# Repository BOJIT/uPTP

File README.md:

# uPTP

The smallest, cheapest PTP clock that you can make!

## Project Setup

1. Clone Project to your computer

2. Ensure that you have west installed somehere (I usually put it in `<GIT_REPO>/.venv`, as VSCode will usually launch it automatically.)

- `python -m venv .venv`
- `source .venv/bin/activate`
- `pip install west`

3. Run West Init Locally against the West YAML file: `west init -l software/app

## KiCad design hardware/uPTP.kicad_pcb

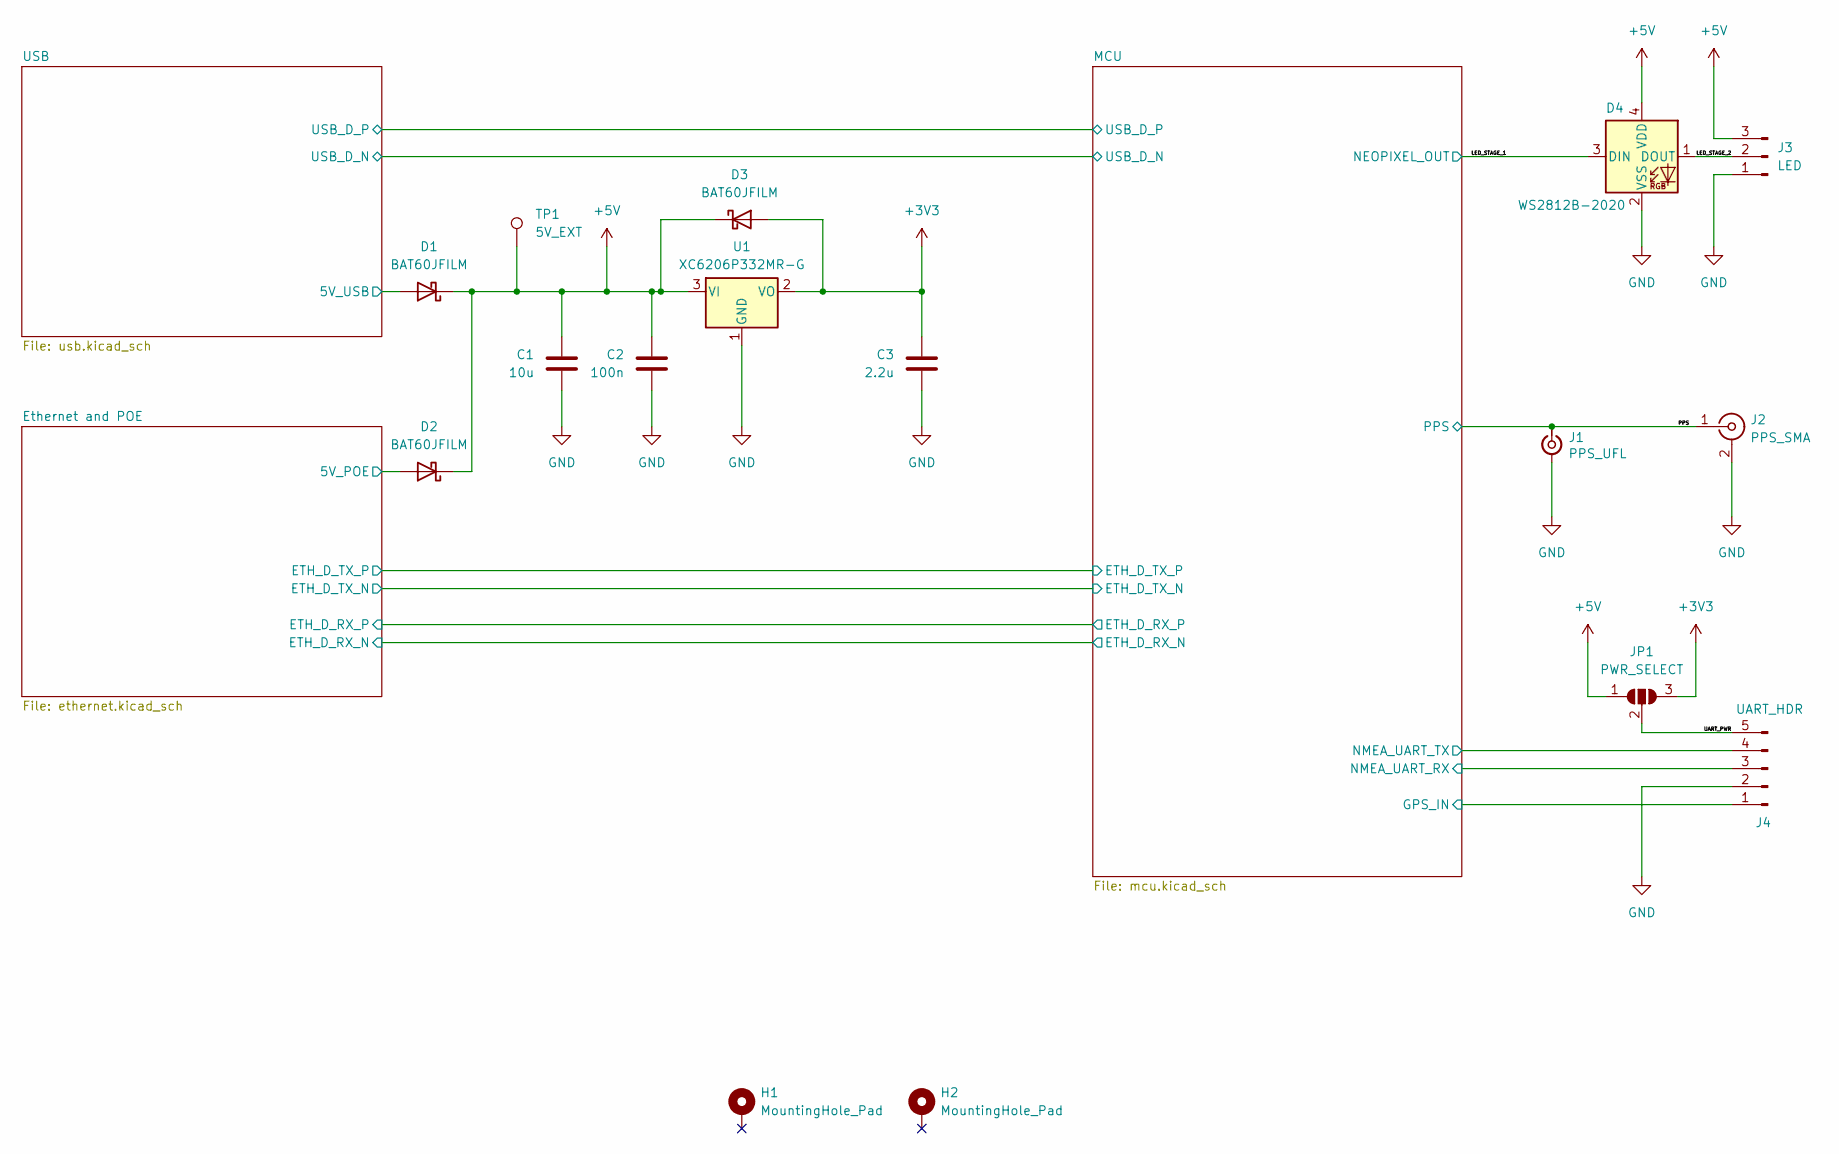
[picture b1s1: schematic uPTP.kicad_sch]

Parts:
C1: 10u; C_0603_1608Metric; LCSC Part C19702
C2: 100n; C_0402_1005Metric; LCSC Part C1525
C3: 2.2u; C_0402_1005Metric; LCSC Part C12530
D1, D2, D3: BAT60JFILM; D_SOD-323; LCSC Part C133103
D4: WS2812B-2020; LED_WS2812B-2020_PLCC4_2.0x2.0mm; LCSC Part C965555
H1, H2: MountingHole_Pad; MountingHole_3.2mm_M3_Pad
J1: PPS_UFL; IPEX-SMD_HC-RF-IPEX0303-01; LCSC Part C2894919
J2: PPS_SMA; SMA_Samtec_SMA-J-P-H-ST-EM1_EdgeMount
J3: LED; PinHeader_1x03_P1.27mm_Vertical
J4: UART_HDR; PinHeader_1x05_P2.54mm_Horizontal
JP1: PWR_SELECT; SolderJumper-3_P1.3mm_Open_RoundedPad1.0x1.5mm_NumberLabels
TP1: 5V_EXT; TestPoint_Pad_D1.5mm
U1: XC6206P332MR-G; SOT-23-3; LCSC Part C5446

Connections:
+3V3: C3.1, D3.2 (A), JP1.3 (B), U1.2 (VO); also elsewhere on the board
+5V: C1.1, C2.1, D1.1 (K), D2.1 (K), D3.1 (K), D4.4 (VDD), J3.3, JP1.1 (A), TP1.1, U1.3 (VI); also elsewhere on the board
+5V_USB: D1.2 (A); also elsewhere on the board
/Ethernet and POE/ETH_POE_FILT_P: D2.2 (A); also elsewhere on the board
/LED_STAGE_1: D4.3 (DIN); also elsewhere on the board
/LED_STAGE_2: D4.1 (DOUT), J3.2
/MCU/GPS_IN: J4.1; also elsewhere on the board
/MCU/NMEA_UART_RX: J4.3; also elsewhere on the board
/MCU/NMEA_UART_TX: J4.4; also elsewhere on the board
/PPS: J1.1 (In), J2.1 (In); also elsewhere on the board
/UART_PWR: J4.5, JP1.2 (C)
GND: C1.2, C2.2, C3.2, D4.2 (VSS), J1.2 (Ext), J2.2 (Ext), J3.1, J4.2, U1.1 (GND); also elsewhere on the board

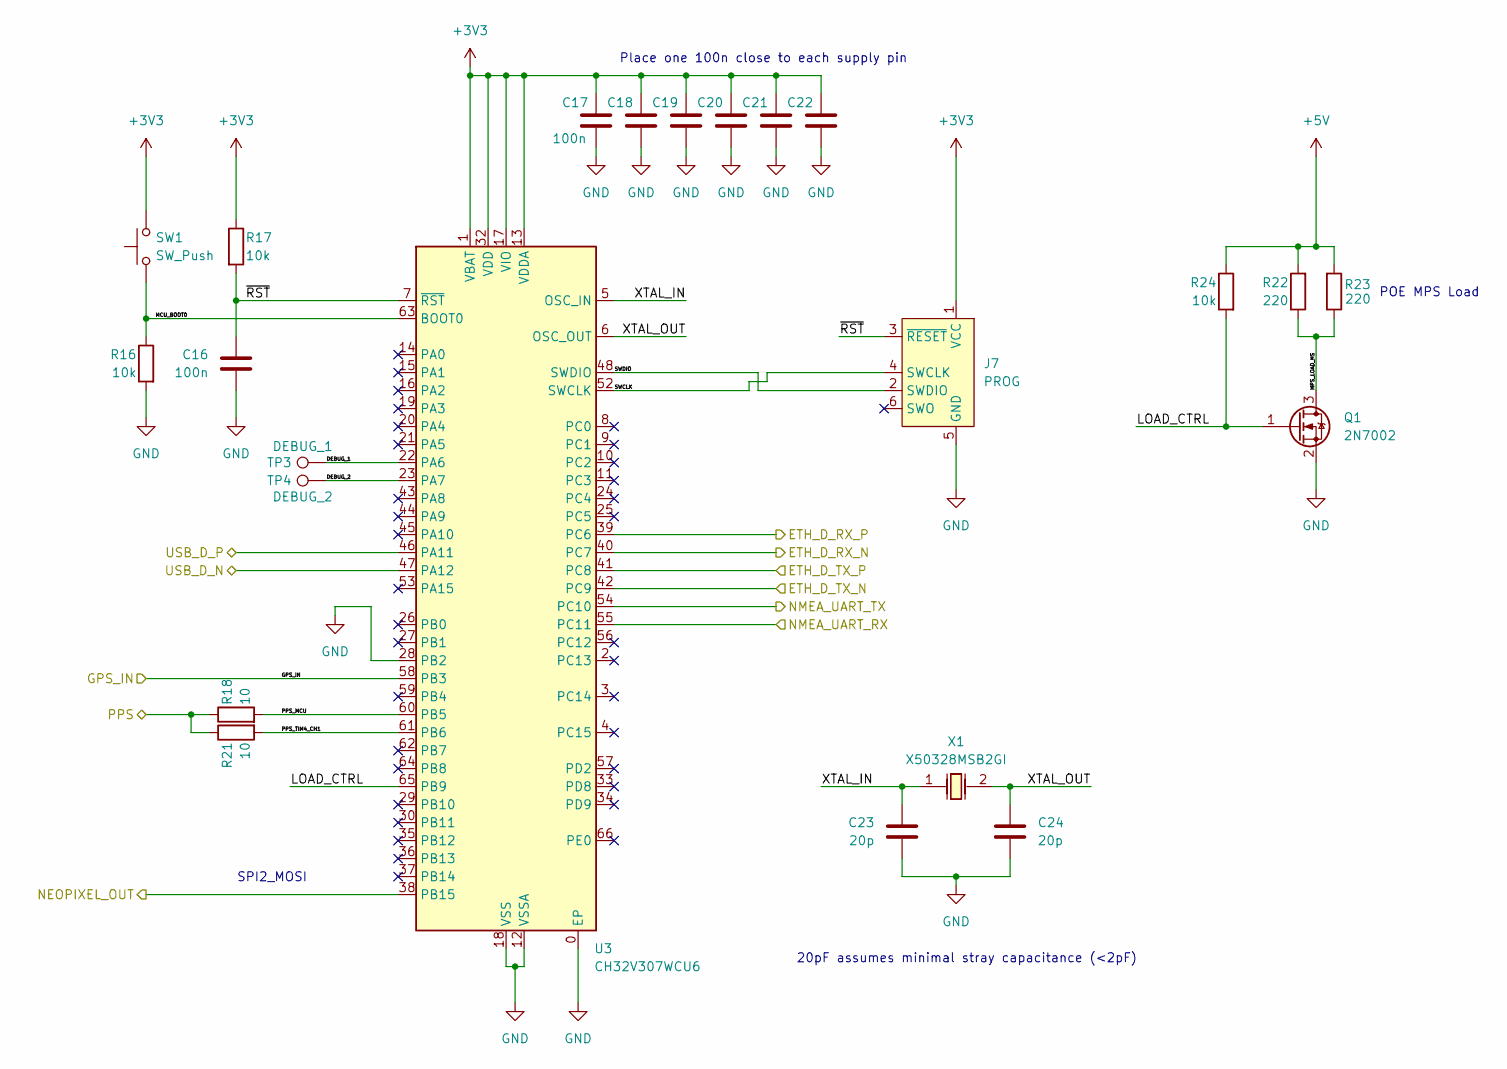
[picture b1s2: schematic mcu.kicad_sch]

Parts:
C16, C17, C18, C19, C20, C21, C22: 100n; C_0402_1005Metric; LCSC Part C1525
C23, C24: 20p; C_0402_1005Metric; LCSC Part C1554
J7: PROG; Tag-Connect_TC2030-IDC-NL_2x03_P1.27mm_Vertical
Q1: 2N7002; SOT-23; LCSC Part C8545
R16, R17, R24: 10k; R_0402_1005Metric; LCSC Part C25744
R18, R21: 10; R_0402_1005Metric; LCSC Part C25077
R22, R23: 220; R_0603_1608Metric; LCSC Part C22962
SW1: SW_Push; SW-SMD_L3.9-W3.0-P4.45; LCSC Part C720477
TP3: DEBUG_1; TestPoint_Pad_D1.5mm
TP4: DEBUG_2; TestPoint_Pad_D1.5mm
U3: CH32V307WCU6; QFN-68_L8.0-W8.0-P0.40-BL-EP6.7; LCSC Part C5142795
X1: X50328MSB2GI; CRYSTAL-SMD_L5.0-W3.2; LCSC Part C115962

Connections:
+3V3: C17.1, C18.1, C19.1, C20.1, C21.1, C22.1, J7.1 (VCC), R17.1, SW1.2, U3.1 (VBAT), U3.13 (VDDA), U3.17 (VIO), U3.31 (VIO), U3.32 (VDD), U3.50 (VDD), U3.51 (VIO), U3.67 (VIO), U3.68 (VDD); also elsewhere on the board
+5V: R22.2, R23.2, R24.1; also elsewhere on the board
/Ethernet and POE/ETH_D_RX_N: U3.40 (PC7); also elsewhere on the board
/Ethernet and POE/ETH_D_RX_P: U3.39 (PC6); also elsewhere on the board
/Ethernet and POE/ETH_D_TX_N: U3.42 (PC9); also elsewhere on the board
/Ethernet and POE/ETH_D_TX_P: U3.41 (PC8); also elsewhere on the board
/LED_STAGE_1: U3.38 (PB15); also elsewhere on the board
/MCU/DEBUG_1: TP3.1, U3.22 (PA6)
/MCU/DEBUG_2: TP4.1, U3.23 (PA7)
/MCU/GPS_IN: U3.58 (PB3); also elsewhere on the board
/MCU/LOAD_CTRL: Q1.1 (G), R24.2, U3.65 (PB9)
/MCU/MCU_BOOT0: R16.1, SW1.1, U3.63 (BOOT0)
/MCU/MPS_LOAD_HS: Q1.3 (D), R22.1, R23.1
/MCU/NMEA_UART_RX: U3.55 (PC11); also elsewhere on the board
/MCU/NMEA_UART_TX: U3.54 (PC10); also elsewhere on the board
/MCU/PPS_MCU: R18.2, U3.60 (PB5)
/MCU/PPS_TIM4_CH1: R21.2, U3.61 (PB6)
/MCU/SWCLK: J7.4 (SWCLK), U3.52 (SWCLK)
/MCU/SWDIO: J7.2 (SWDIO), U3.48 (SWDIO)
/MCU/USB_D_N: U3.47 (PA12); also elsewhere on the board
/MCU/USB_D_P: U3.46 (PA11); also elsewhere on the board
/MCU/XTAL_IN: C23.1, U3.5 (OSC_IN), X1.1
/MCU/XTAL_OUT: C24.1, U3.6 (OSC_OUT), X1.2
/MCU/~RST: C16.1, J7.3 (~RESET), R17.2, U3.7 (~RST)
/PPS: R18.1, R21.1; also elsewhere on the board
GND: C16.2, C17.2, C18.2, C19.2, C20.2, C21.2, C22.2, C23.2, C24.2, J7.5 (GND), Q1.2 (S), R16.2, U3.0 (EP), U3.12 (VSSA), U3.18 (VSS), U3.28 (PB2), U3.49 (VSS), U3.69 (VSS); also elsewhere on the board

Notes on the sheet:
SPI2_MOSI
20pF assumes minimal stray capacitance (<2pF)
POE MPS Load
Place one 100n close to each supply pin

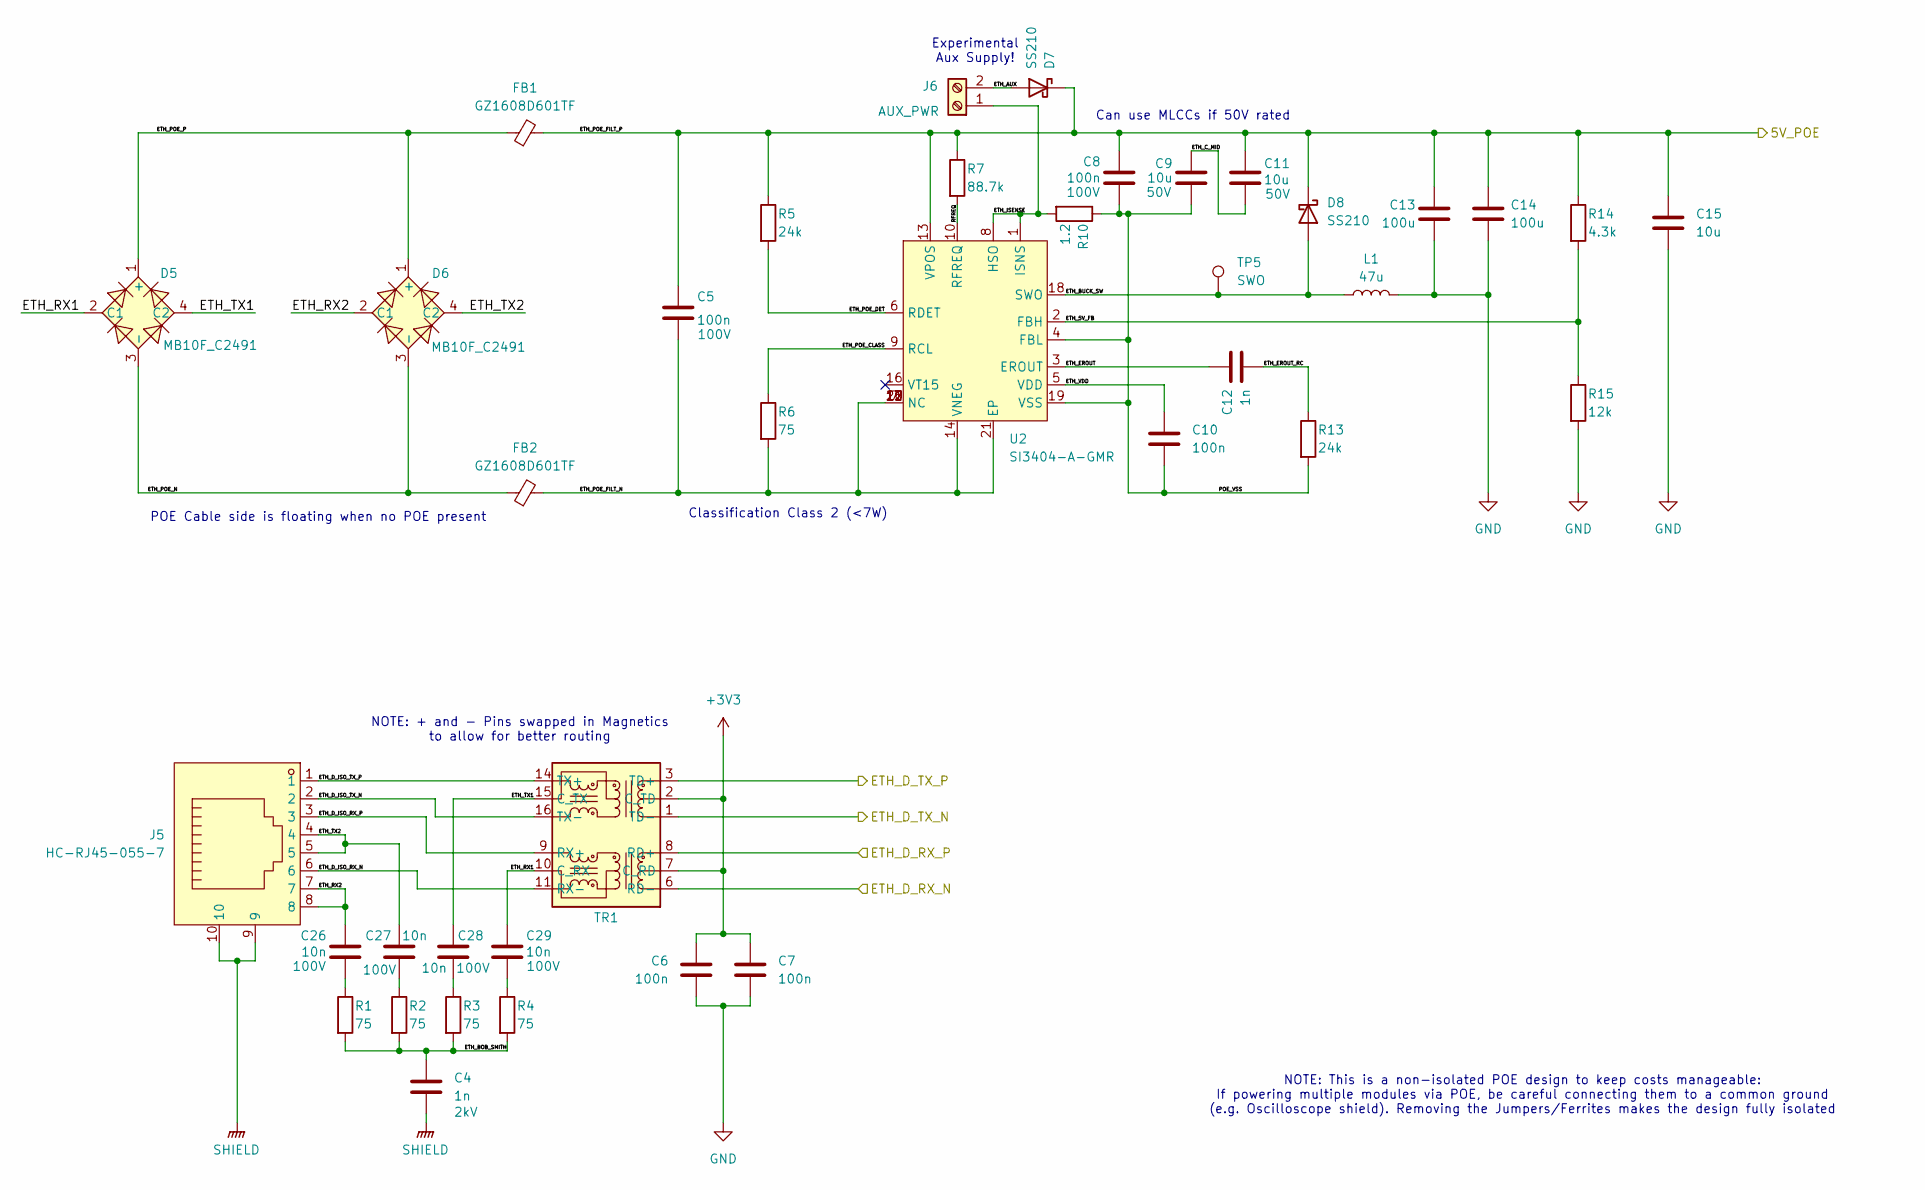
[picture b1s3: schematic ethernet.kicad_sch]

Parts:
C4: 1n; C_1206_3216Metric; LCSC Part C9196
C5, C8: 100n; C_0805_2012Metric; LCSC Part C28233
C6, C7, C10: 100n; C_0402_1005Metric; LCSC Part C1525
C9, C11: 10u; C_0805_2012Metric; LCSC Part C440198
C12: 1n; C_0402_1005Metric; LCSC Part C1523
C13, C14: 100u; C_1206_3216Metric; LCSC Part C15008
C15: 10u; C_0603_1608Metric; LCSC Part C19702
C26, C27, C28, C29: 10n; C_0402_1005Metric; LCSC Part C527014
D5, D6: MB10F_C2491; DIO-BG-SMD_4P-L4.9-W4.0-P2.54-LS7.0-BR; LCSC Part C2491
D7, D8: SS210; D_SMA; LCSC Part C14996
FB1, FB2: GZ1608D601TF; R_0603_1608Metric; LCSC Part C1002
J5: HC-RJ45-055-7; RJ45-SMD_HC-RJ45-055-7_1; LCSC Part C3000213
J6: AUX_PWR; TerminalBlock_Phoenix_MPT-0,5-2-2.54_1x02_P2.54mm_Horizontal
L1: 47u; L_Changjiang_FXL0630; LCSC Part C475913
R1, R2, R3, R4, R6: 75; R_0402_1005Metric; LCSC Part C25133
R5, R13: 24k; R_0402_1005Metric; LCSC Part C25769
R7: 88.7k; R_0402_1005Metric; LCSC Part C170366
R10: 1.2; R_0402_1005Metric; LCSC Part C2998063
R14: 4.3k; R_0402_1005Metric; LCSC Part C25899
R15: 12k; R_0402_1005Metric; LCSC Part C25752
TP5: SWO; TestPoint_Pad_D1.5mm
TR1: Ethernet Magnetics; B1608S; LCSC Part C507596
U2: SI3404-A-GMR; QFN-20-1EP_4x4mm_P0.5mm_EP2.6x2.6mm; LCSC Part C461934

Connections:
+3V3: C6.1, C7.1, TR1.2 (C_TD), TR1.7 (C_RD); also elsewhere on the board
/Ethernet and POE/ETH_5V_FB: R14.2, R15.1, U2.2 (FBH)
/Ethernet and POE/ETH_AUX: D7.2 (A), J6.2
/Ethernet and POE/ETH_BOB_SMITH: C4.1, R1.2, R2.2, R3.2, R4.2
/Ethernet and POE/ETH_BUCK_SW: D8.2 (A), L1.1, TP5.1, U2.18 (SWO)
/Ethernet and POE/ETH_C_MID: C9.1, C11.2
/Ethernet and POE/ETH_D_ISO_RX_N: J5.6, TR1.11 (RX-)
/Ethernet and POE/ETH_D_ISO_RX_P: J5.3, TR1.9 (RX+)
/Ethernet and POE/ETH_D_ISO_TX_N: J5.2, TR1.16 (TX-)
/Ethernet and POE/ETH_D_ISO_TX_P: J5.1, TR1.14 (TX+)
/Ethernet and POE/ETH_D_RX_N: TR1.6 (RD-); also elsewhere on the board
/Ethernet and POE/ETH_D_RX_P: TR1.8 (RD+); also elsewhere on the board
/Ethernet and POE/ETH_D_TX_N: TR1.1 (TD-); also elsewhere on the board
/Ethernet and POE/ETH_D_TX_P: TR1.3 (TD+); also elsewhere on the board
/Ethernet and POE/ETH_EROUT: C12.1, U2.3 (EROUT)
/Ethernet and POE/ETH_EROUT_RC: C12.2, R13.1
/Ethernet and POE/ETH_ISENSE: J6.1, R10.2, U2.1 (ISNS), U2.8 (HSO)
/Ethernet and POE/ETH_POE_CLASS: R6.1, U2.9 (RCL)
/Ethernet and POE/ETH_POE_DET: R5.2, U2.6 (RDET)
/Ethernet and POE/ETH_POE_FILT_N: C5.2, FB2.2, R6.2, U2.7 (NC), U2.11 (NC), U2.12 (NC), U2.14 (VNEG), U2.15 (NC), U2.17 (NC), U2.20 (NC), U2.21 (EP)
/Ethernet and POE/ETH_POE_FILT_P: C5.1, C8.1, C11.1, C13.1, C14.1, C15.1, D7.1 (K), D8.1 (K), FB1.2, R5.1, R7.1, R14.1, U2.13 (VPOS); also elsewhere on the board
/Ethernet and POE/ETH_POE_N: D5.3 (-), D6.3 (-), FB2.1
/Ethernet and POE/ETH_POE_P: D5.1 (+), D6.1 (+), FB1.1
/Ethernet and POE/ETH_RX1: C29.1, D5.2 (C1), TR1.10 (C_RX)
/Ethernet and POE/ETH_RX2: C26.1, D6.2 (C1), J5.7, J5.8
/Ethernet and POE/ETH_TX1: C28.1, D5.4 (C2), TR1.15 (C_TX)
/Ethernet and POE/ETH_TX2: C27.1, D6.4 (C2), J5.4, J5.5
/Ethernet and POE/ETH_VDD: C10.1, U2.5 (VDD)
/Ethernet and POE/POE_VSS: C8.2, C9.2, C10.2, R10.1, R13.2, U2.4 (FBL), U2.19 (VSS)
/Ethernet and POE/RFREQ: R7.2, U2.10 (RFREQ)
GND: C6.2, C7.2, C13.2, C14.2, C15.2, L1.2, R15.2; also elsewhere on the board
unnamed: C26.2, R1.1
unnamed: C27.2, R2.1
unnamed: C28.2, R3.1
unnamed: C29.2, R4.1
SHIELD: C4.2, J5.9, J5.10

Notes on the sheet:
Experimental Aux Supply!
POE Cable side is floating when no POE present
NOTE: + and - Pins swapped in Magnetics to allow for better routing
Classification Class 2 (<7W)
Can use MLCCs if 50V rated
NOTE: This is a non-isolated POE design to keep costs manageable: If powering multiple modules via POE, be careful connecting them to a common ground (e.g. Oscilloscope shield). Removing the Jumpers/Ferrites makes the design fully isolated

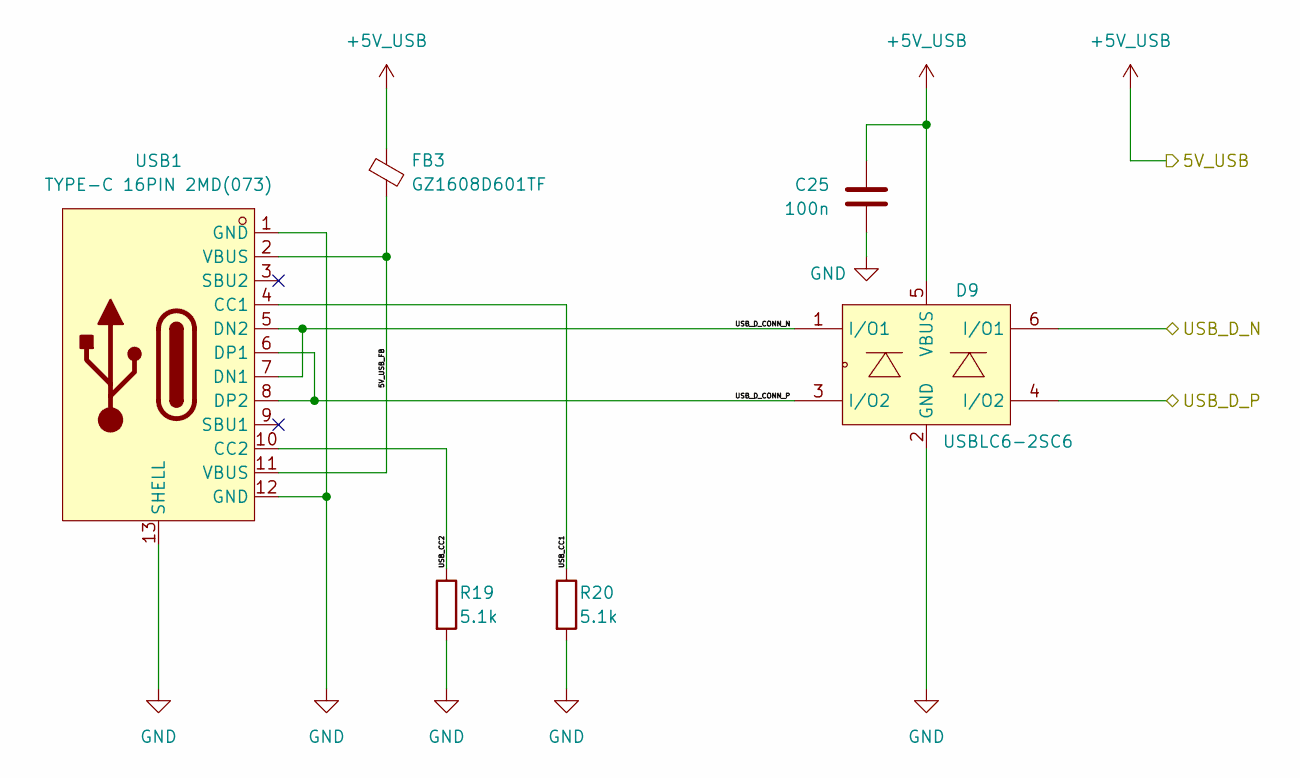
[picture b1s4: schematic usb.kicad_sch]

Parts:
C25: 100n; C_0402_1005Metric; LCSC Part C1525
D9: USBLC6-2SC6; SOT-23-6_L2.9-W1.6-P0.95-LS2.8-BL; LCSC Part C7519
FB3: GZ1608D601TF; R_0603_1608Metric; LCSC Part C1002
R19, R20: 5.1k; R_0402_1005Metric; LCSC Part C25905
USB1: TYPE-C 16PIN 2MD(073); USB-C-SMD_TYPE-C-16PIN; LCSC Part C2765186

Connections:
+5V_USB: C25.1, D9.5 (VBUS), FB3.1; also elsewhere on the board
/MCU/USB_D_N: D9.6 (I/O1); also elsewhere on the board
/MCU/USB_D_P: D9.4 (I/O2); also elsewhere on the board
/USB/5V_USB_FB: FB3.2, USB1.2 (VBUS), USB1.11 (VBUS)
/USB/USB_CC1: R20.1, USB1.4 (CC1)
/USB/USB_CC2: R19.1, USB1.10 (CC2)
/USB/USB_D_CONN_N: D9.1 (I/O1), USB1.5 (DN2), USB1.7 (DN1)
/USB/USB_D_CONN_P: D9.3 (I/O2), USB1.6 (DP1), USB1.8 (DP2)
GND: C25.2, D9.2 (GND), R19.2, R20.2, USB1.1 (GND), USB1.12 (GND), USB1.13 (SHELL); also elsewhere on the board

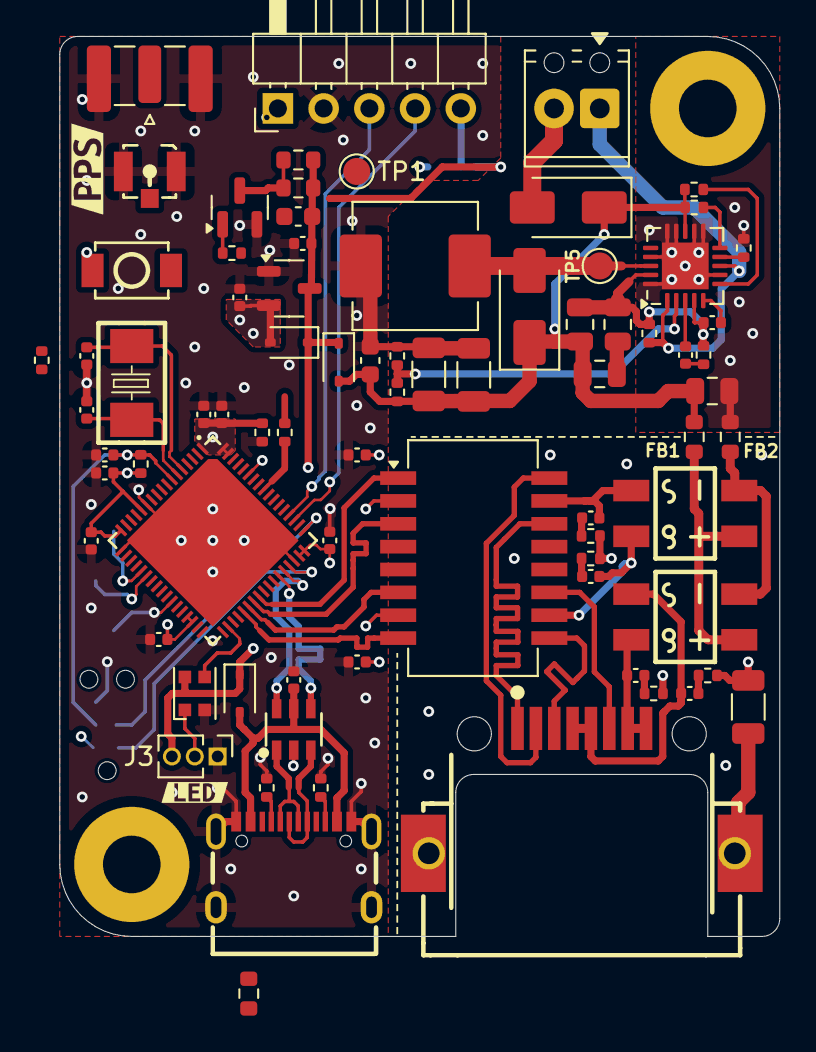
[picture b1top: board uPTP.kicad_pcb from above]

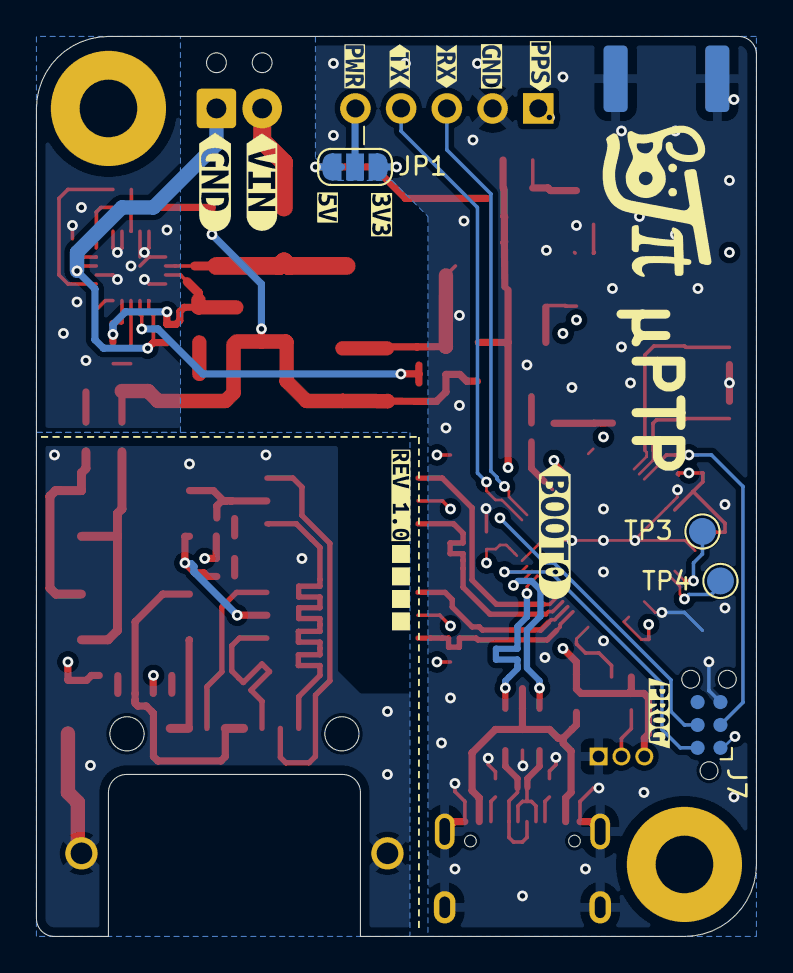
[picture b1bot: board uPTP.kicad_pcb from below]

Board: 4 copper layers, 40.0 x 50.0 mm, 99 parts (16 on the bottom side), 64 nets.

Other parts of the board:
kibuzzard-68B2C77A: G***; kibuzzard-68B2C77A
kibuzzard-68B2C79E: G***; kibuzzard-68B2C79E
kibuzzard-68B2D2A2: G***; kibuzzard-68B2D2A2
kibuzzard-68B2D2B0: G***; kibuzzard-68B2D2B0
kibuzzard-68B2D2D8: G***; kibuzzard-68B2D2D8
kibuzzard-68B2D2E2: G***; kibuzzard-68B2D2E2
kibuzzard-68B2D3F7: G***; kibuzzard-68B2D3F7
kibuzzard-68B2D9A3: G***; kibuzzard-68B2D9A3
kibuzzard-68B2D28B: G***; kibuzzard-68B2D28B
kibuzzard-68B2D264: G***; kibuzzard-68B2D264
kibuzzard-68B2D304: G***; kibuzzard-68B2D304
kibuzzard-68B2D348: G***; kibuzzard-68B2D348
kibuzzard-68B2D367: G***; kibuzzard-68B2D367
kibuzzard-68B2D434: G***; kibuzzard-68B2D434
kibuzzard-696D5DC7: G***; kibuzzard-696D5DC7

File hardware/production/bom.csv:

Designator,Footprint,Quantity,Value,LCSC Part #
"C1, C15",0603,2,10u,C19702
"C10, C16, C17, C18, C19, C2, C20, C21, C22, C25, C6, C7",0402,12,100n,C1525
"C11, C9",0805,2,10u,C440198
C12,0402,1,1n,C1523
"C13, C14",1206,2,100u,C15008
"C23, C24",0402,2,20p,C1554
C3,0402,1,2.2u,C12530
C4,1206,1,1n,C9196
"C5, C8",0805,2,100n,C28233
"D1, D2, D3",D_SOD-323,3,BAT60JFILM,C133103
D4,LED_WS2812B-2020_PLCC4_2.0x2.0mm,1,WS2812B-2020,C965555
"D5, D6",DIO-BG-SMD_4P-L4.9-W4.0-P2.54-LS7.0-BR,2,MB10F_C2491,C2491
"D7, D8",D_SMA,2,SS210,C14996
D9,SOT-23-6_L2.9-W1.6-P0.95-LS2.8-BL,1,USBLC6-2SC6,C7519
"FB1, FB2",0603,2,GZ1608D601TF,C1002
J1,IPEX-SMD_HC-RF-IPEX0303-01,1,PPS_UFL,C2894919
J5,RJ45-SMD_HC-RJ45-055-7_1,1,HC-RJ45-055-7,C3000213
L1,L_Changjiang_FXL0630,1,47u,C475913
"R1, R2, R3, R4, R6",0402,5,75,C25133
R10,0402,1,1.2,C2998063
"R13, R5",0402,2,24k,C25769
R14,0402,1,4.3k,C25899
R15,0402,1,12k,C25752
"R16, R17",0402,2,10k,C25744
R18,0402,1,10,C25077
"R19, R20",0402,2,5.1k,C25905
R7,0402,1,88.7k,C170366
TR1,B1608S,1,Ethernet Magnetics,C507596
U1,SOT-23-3,1,XC6206P332MR-G,C5446
U2,QFN-20-1EP_4x4mm_P0.5mm_EP2.6x2.6mm,1,SI3404-A-GMR,C461934
U3,QFN-68_L8.0-W8.0-P0.40-BL-EP6.7,1,CH32V307WCU6,C5142795
USB1,USB-C-SMD_TYPE-C-16PIN,1,TYPE-C 16PIN 2MD(073),C2765186
X1,CRYSTAL-SMD_L5.0-W3.2,1,X50328MSB2GI,C115962

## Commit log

2025-06-01 Add first files
2025-06-01 Key components
2025-06-03 Some more handy components
2025-06-03 Add magnetics
2025-06-03 Nice first render
2025-06-04 POE CTRL?
2025-06-04 Backup progress
2025-06-05 POE layout considerationa
2025-06-06 Vaguely convincing render...
2025-06-06 Component selection mostly done
2025-06-06 Done for the day
2025-07-09 Prep for change to SI3404 https://www.skyworksinc.com/-/media/Skyworks/SL/documents/public/application-notes/an1130-si3404-06x-dg.pdf
2025-07-11 Add SI3404 part
2025-07-12 Add XTAL, rough POE Schematic
2025-07-13 Neaten up schematic hierarchy
2025-07-13 Confirm all part footprints, start rought layout
2025-07-13 Tidy up layout
2025-08-04 Set reqs for trace widths
2025-08-10 Change pin layout to make Ethernet Routing nicer
2025-08-29 Route one
2025-08-29 All length match
2025-08-29 ISO ETH Section Done
2025-08-29 All footprints 3D plus some more routing
2025-08-29 Fix aux pwr oops
2025-08-29 Backup before relayout
2025-08-29 Correct misunderstandings, mostly there
2025-08-29 Routed board, first draft
2025-08-29 Routed, need to do DRC
2025-08-30 Clear all easy violations
2025-08-30 All DRCs cleared
2025-08-30 Artwork added
2025-08-30 Add rounded track overlay
2025-08-30 Add teardrops
2025-08-30 Re-link rounded to be default
2025-08-30 Fix BOM entries, should be good to go
2025-08-30 Allow assembly files to be checked in
2025-08-30 Ready to send off!
2025-08-30 Update IBOM
2025-09-09 Add West Manifest
2025-09-09 Move to root?
2025-09-09 Nicer structure
2025-09-09 Basic board support template for Zephyr
2025-09-09 Custom Board Support Works!
2025-09-09 Use correct pin variant
2025-09-09 Remap uPTP hardware to new UART pins
2025-09-10 Add basic OpenOCD config
2025-09-10 Nice logging backend example
2025-09-11 Add EVK Locally for testing
2025-09-11 Fix docs
2025-09-11 Change to local EVK
2025-09-11 Correct HSE Frequnecy
2025-09-12 Add option to build for STM32 target too
2025-09-13 Some rough structure
2025-09-20 Net Config
2025-09-21 Trims to get things running on smaller RAM footprint
2025-09-21 Add local overlay for alternative RAM configuration
2025-09-29 More experiments
2025-12-14 Useful debugging
2025-12-14 Add Ethernet to the uPTP board - works!
2025-12-31 Add WS2812b SPI mode via test point 4 (PA7)
2026-01-01 Working SPI
2026-01-01 Basic Test RGB
2026-01-02 KConfig optimize
2026-01-08 Disable LED strip for now, get things tested for CH32V307 ethernet PR
2026-01-09 rename to work on case-sensitive filesystem, fix CI
2026-01-09 MDNS and DNS-SD working
2026-01-09 Update manifest
2026-01-09 Test HW multicast filter
2026-01-11 Test Ethernet Driver fixes, with LED
2026-01-11 Add PTP clock driver template
    Track PTP clock branch here
    Move ptp clock out of here
2026-01-11 Add appropriate init flags
2026-01-11 Disable LED strip for now, get things tested for CH32V307 ethernet PR (#2)
    * Disable LED strip for now, get things tested for CH32V307 ethernet PR
    * rename to work on case-sensitive filesystem, fix CI
    * MDNS and DNS-SD working
    * Update manifest
    * Test HW multicast filter
    * Test Ethernet Driver fixes, with LED
2026-01-18 First of listed hardware changes, need verification
2026-01-25 Fix pullup
2026-02-07 PTP and DNS-SD working with both target zephyr commits
2026-02-07 Move to centralised EVK defs
    Example of board variants for flash size
2026-02-21 backup
2026-02-24 Get rid of local dev board copy
2026-02-24 Add overlay for PTP clock
